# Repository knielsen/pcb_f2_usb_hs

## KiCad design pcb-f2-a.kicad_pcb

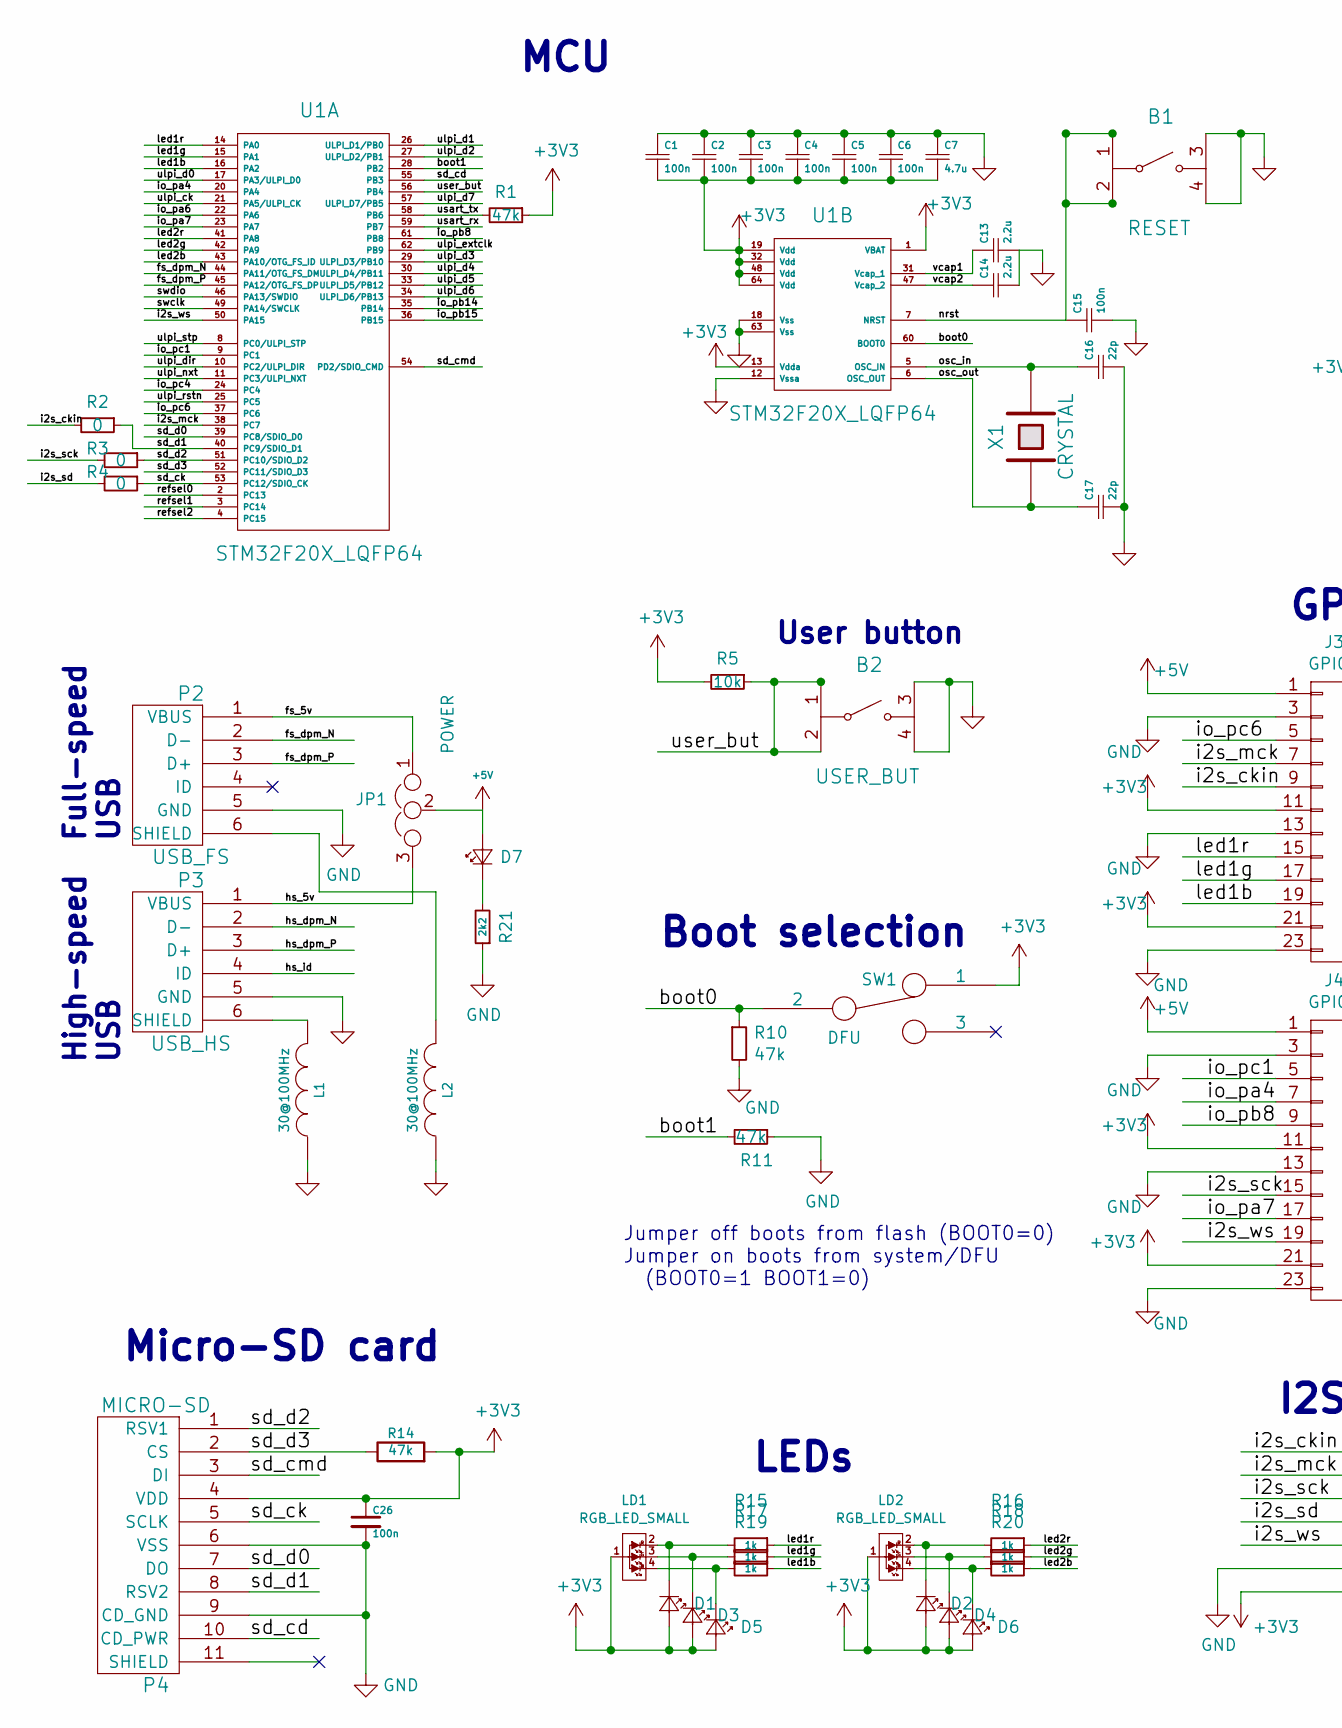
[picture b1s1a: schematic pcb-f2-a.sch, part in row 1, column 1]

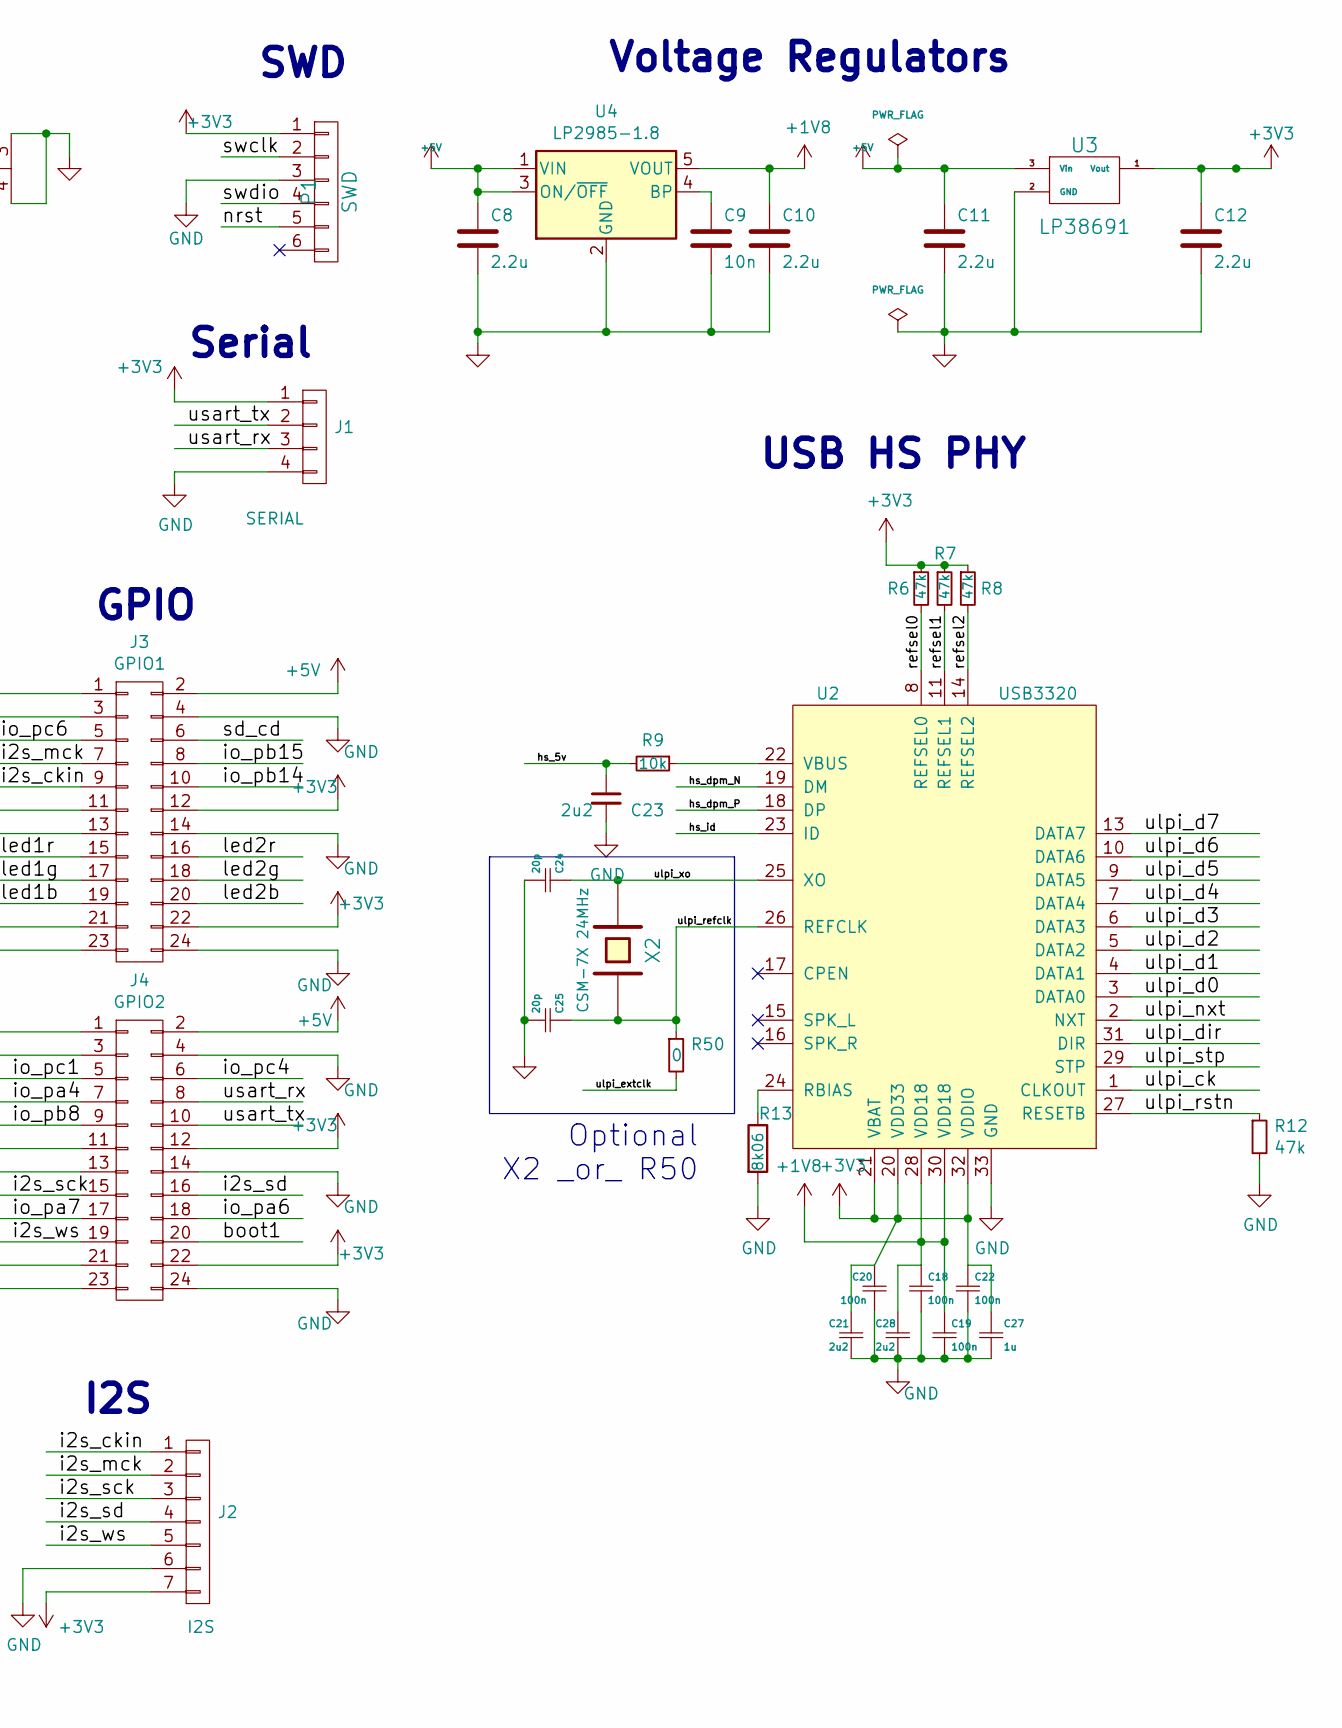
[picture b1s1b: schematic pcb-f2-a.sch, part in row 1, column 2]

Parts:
B1: RESET; SWITCH_FSMJSMA
B2: USER_BUT; SWITCH_FSMJSMA
C1, C2, C3, C4, C5, C6, C15, C18, C19, C20, C22, C26: 100n; C_0603
C7: 4.7u; C_0805
C8, C10, C11, C12, C13, C14: 2.2u; C_0805
C9: 10n; C_0603
C16, C17: 22p; C_0603
C21, C23, C28: 2u2; C_0805
C24, C25: 20p; C_0603
C27: 1u; C_0805
D1, D2, D3, D4, D5, D6, D7: LED_Small; LED_0805_HandSoldering
J1: SERIAL; Pin_Header_Straight_1x04_Pitch2.54mm
J2: I2S; Pin_Header_Straight_1x07_Pitch2.54mm
J3: GPIO1; Socket_Strip_Straight_2x12_Pitch2.54mm
J4: GPIO2; Socket_Strip_Straight_2x12_Pitch2.54mm
JP1: POWER; Pin_Header_Straight_1x03_Pitch2.54mm
L1, L2: 30@100MHz; C_0603
LD1, LD2: RGB_LED_SMALL; RGB_0603
P1: SWD; Pin_Header_Straight_1x06_Pitch2.54mm
P2: USB_FS; 10103594-0001LF
P3: USB_HS; 10103594-0001LF
P4: MICRO-SD; SD_502774
R1, R6, R7, R8, R10, R11, R12, R14: 47k; R_0805
R2, R3, R4, R50: 0; R_0805
R5, R9: 10k; R_0805
R13: 8k06; R_0805
R15, R16, R17, R18, R19, R20: 1k; R_0805
R21: 2k2; R_0805
SW1: DFU; switch_msk_12c02
U1: STM32F20X_LQFP64; LQFP_64
U2: USB3320; QFN-32-USB-3320
U3: LP38691; TO-252-3
U4: LP2985-1.8; SOT-23-5
X1: CRYSTAL; 2-SOJ
X2: CSM-7X 24MHz; Crystal_SMD_HC49-US

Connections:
+1V8: C10.1, C18.1, C19.1, C28.1, U2.28 (VDD18), U2.30 (VDD18), U4.5 (VOUT)
+3V3: C1.2, C2.2, C3.2, C4.2, C5.2, C6.2, C7.2, C12.1, C20.1, C21.1, C22.1, C26.1, C27.1, D1.2 (A), D2.2 (A), D3.2 (A), D4.2 (A), D5.2 (A), D6.2 (A), J1.1, J2.7, J3.11, J3.12, J3.21, J3.22, J4.11, J4.12, J4.21, J4.22, LD1.1 (AG), LD2.1 (AG), P1.1, P4.4 (VDD), R1.1, R5.2, R6.1, R7.1, R8.1, R14.2, SW1.1, U1.1 (VBAT), U1.13 (Vdda), U1.19 (Vdd), U1.32 (Vdd), U1.48 (Vdd), U1.64 (Vdd), U2.20 (VDD33), U2.21 (VBAT), U2.32 (VDDIO), U3.1 (Vout)
+5V: C8.1, C11.1, D7.2 (A), J3.1, J3.2, J4.1, J4.2, JP1.2, U3.3 (Vin), U4.1 (VIN), U4.3 (ON/~OFF~)
/boot0: R10.1, SW1.2, U1.60 (BOOT0)
/boot1: J4.20, R11.2, U1.28 (PB2)
/fs_5v: JP1.1, P2.1 (VBUS)
/fs_dpm_N: P2.2 (D-), U1.44 (PA11/OTG_FS_DM)
/fs_dpm_P: P2.3 (D+), U1.45 (PA12/OTG_FS_DP)
/hs_5v: C23.1, JP1.3, P3.1 (VBUS), R9.2
/hs_dpm_N: P3.2 (D-), U2.19 (DM)
/hs_dpm_P: P3.3 (D+), U2.18 (DP)
/hs_id: P3.4 (ID), U2.23 (ID)
/i2s_ckin: J2.1, J3.9, R2.2
/i2s_mck: J2.2, J3.7, U1.38 (PC7)
/i2s_sck: J2.3, J4.15, R3.2
/i2s_sd: J2.4, J4.16, R4.2
/i2s_ws: J2.5, J4.19, U1.50 (PA15)
/io_pa4: J4.7, U1.20 (PA4)
/io_pa6: J4.18, U1.22 (PA6)
/io_pa7: J4.17, U1.23 (PA7)
/io_pb8: J4.9, U1.61 (PB8)
/io_pb14: J3.10, U1.35 (PB14)
/io_pb15: J3.8, U1.36 (PB15)
/io_pc1: J4.5, U1.9 (PC1)
/io_pc4: J4.6, U1.24 (PC4)
/io_pc6: J3.5, U1.37 (PC6)
/led1b: J3.19, R19.1, U1.16 (PA2)
/led1g: J3.17, R17.1, U1.15 (PA1)
/led1r: J3.15, R15.1, U1.14 (PA0)
/led2b: J3.20, R20.1, U1.43 (PA10/OTG_FS_ID)
/led2g: J3.18, R18.1, U1.42 (PA9)
/led2r: J3.16, R16.1, U1.41 (PA8)
/nrst: B1.1, B1.2, C15.1, P1.5, U1.7 (NRST)
/osc_in: C16.1, U1.5 (OSC_IN), X1.2
/osc_out: C17.1, U1.6 (OSC_OUT), X1.1
/refsel0: R6.2, U1.2 (PC13), U2.8 (REFSEL0)
/refsel1: R7.2, U1.3 (PC14), U2.11 (REFSEL1)
/refsel2: R8.2, U1.4 (PC15), U2.14 (REFSEL2)
/sd_cd: J3.6, P4.10 (CD_PWR), U1.55 (PB3)
/sd_ck: P4.5 (SCLK), R4.1, U1.53 (PC12/SDIO_CK)
/sd_cmd: P4.3 (DI), U1.54 (PD2/SDIO_CMD)
/sd_d0: P4.7 (DO), U1.39 (PC8/SDIO_D0)
/sd_d1: P4.8 (RSV2), R2.1, U1.40 (PC9/SDIO_D1)
/sd_d2: P4.1 (RSV1), R3.1, U1.51 (PC10/SDIO_D2)
/sd_d3: P4.2 (CS), R14.1, U1.52 (PC11/SDIO_D3)
/swclk: P1.2, U1.49 (PA14/SWCLK)
/swdio: P1.4, U1.46 (PA13/SWDIO)
/ulpi_ck: U1.21 (PA5/ULPI_CK), U2.1 (CLKOUT)
/ulpi_d0: U1.17 (PA3/ULPI_D0), U2.3 (DATA0)
/ulpi_d1: U1.26 (ULPI_D1/PB0), U2.4 (DATA1)
/ulpi_d2: U1.27 (ULPI_D2/PB1), U2.5 (DATA2)
/ulpi_d3: U1.29 (ULPI_D3/PB10), U2.6 (DATA3)
/ulpi_d4: U1.30 (ULPI_D4/PB11), U2.7 (DATA4)
/ulpi_d5: U1.33 (ULPI_D5/PB12), U2.9 (DATA5)
/ulpi_d6: U1.34 (ULPI_D6/PB13), U2.10 (DATA6)
/ulpi_d7: U1.57 (ULPI_D7/PB5), U2.13 (DATA7)
/ulpi_dir: U1.10 (PC2/ULPI_DIR), U2.31 (DIR)
/ulpi_extclk: R50.2, U1.62 (PB9)
/ulpi_nxt: U1.11 (PC3/ULPI_NXT), U2.2 (NXT)
/ulpi_refclk: C25.1, R50.1, U2.26 (REFCLK), X2.1
/ulpi_rstn: R12.1, U1.25 (PC5), U2.27 (RESETB)
/ulpi_stp: U1.8 (PC0/ULPI_STP), U2.29 (STP)
/ulpi_xo: C24.1, U2.25 (XO), X2.2
/usart_rx: J1.3, J4.8, U1.59 (PB7)
/usart_tx: J1.2, J4.10, R1.2, U1.58 (PB6)
/user_but: B2.1, B2.2, R5.1, U1.56 (PB4)
/vcap1: C13.1, U1.31 (Vcap_1)
/vcap2: C14.1, U1.47 (Vcap_2)
GND: B1.3, B1.4, B2.3, B2.4, C1.1, C2.1, C3.1, C4.1, C5.1, C6.1, C7.1, C8.2, C9.2, C10.2, C11.2, C12.2, C13.2, C14.2, C15.2, C16.2, C17.2, C18.2, C19.2, C20.2, C21.2, C22.2, C23.2, C24.2, C25.2, C26.2, C27.2, C28.2, J1.4, J2.6, J3.3, J3.4, J3.13, J3.14, J3.23, J3.24, J4.3, J4.4, J4.13, J4.14, J4.23, J4.24, L1.1, L2.1, P1.3, P2.5 (GND), P3.5 (GND), P4.6 (VSS), P4.9 (CD_GND), R10.2, R11.1, R12.2, R13.2, R21.1, U1.12 (Vssa), U1.18 (Vss), U1.63 (Vss), U2.33 (GND), U3.2 (GND), U4.2 (GND)
unnamed: C9.1, U4.4 (BP)
unnamed: D1.1 (K), LD1.2 (R), R15.2
unnamed: D2.1 (K), LD2.2 (R), R16.2
unnamed: D3.1 (K), LD1.3 (R), R17.2
unnamed: D4.1 (K), LD2.3 (R), R18.2
unnamed: D5.1 (K), LD1.4 (R), R19.2
unnamed: D6.1 (K), LD2.4 (R), R20.2
unnamed: D7.1 (K), R21.2
unnamed: L1.2, P3.6 (SHIELD)
unnamed: L2.2, P2.6 (SHIELD)
unnamed: R9.1, U2.22 (VBUS)
unnamed: R13.1, U2.24 (RBIAS)

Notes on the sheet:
Boot selection
Jumper off boots from flash (BOOT0=0) Jumper on boots from system/DFU (BOOT0=1 BOOT1=0)
MCU
Voltage Regulators
Micro-SD card
SWD
Optional X2 _or_ R50
User button
Full-speed USB
High-speed USB
Serial
LEDs
I2S
USB HS PHY
GPIO

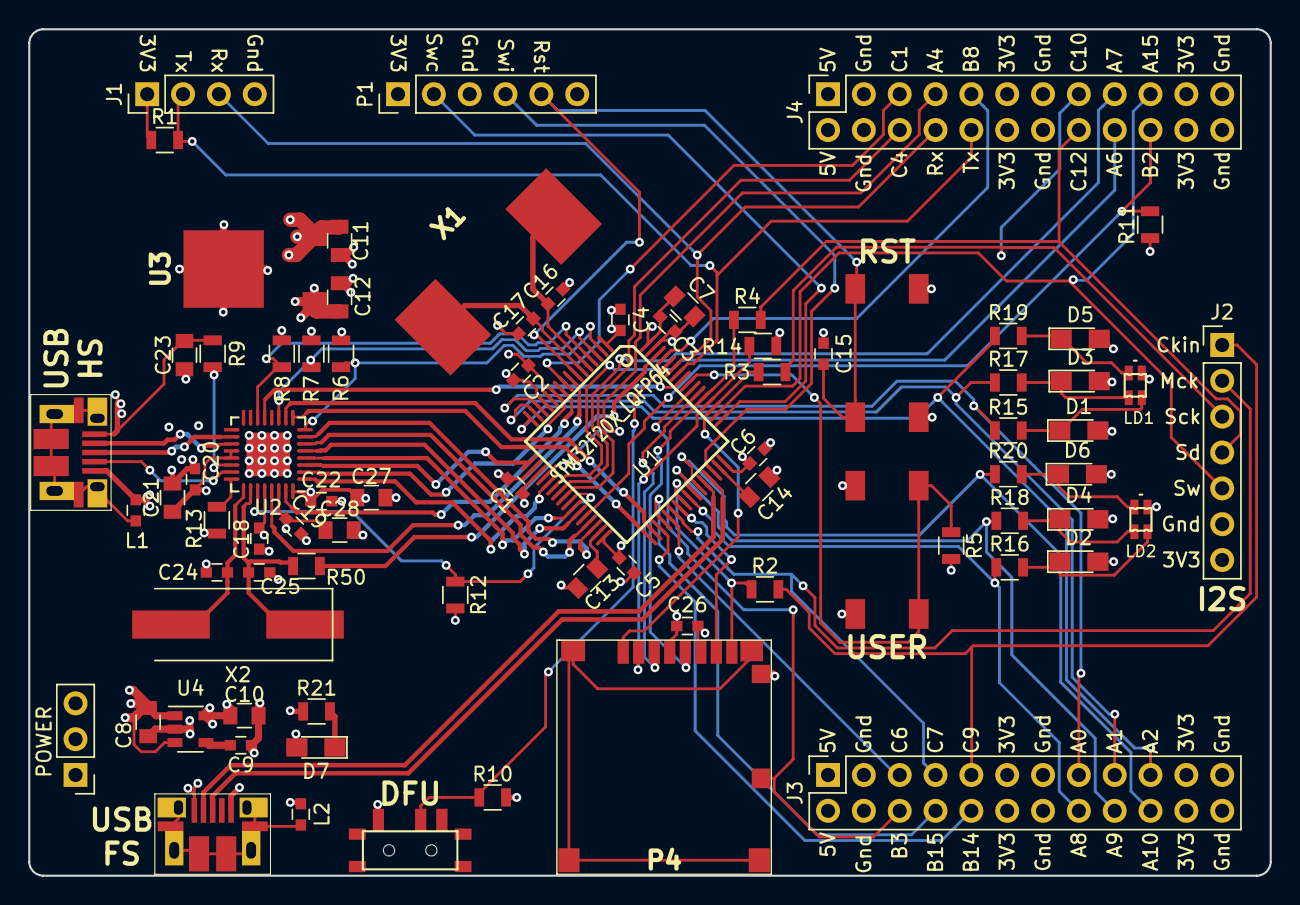
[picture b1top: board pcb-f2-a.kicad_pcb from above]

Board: 4 copper layers, 88.0 x 60.0 mm, 79 parts (0 on the bottom side), 81 nets.

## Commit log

2018-06-14 Rev1, sent for manufacture
2018-07-21 Fix missing back-copper on USB thrugh-hole pads
